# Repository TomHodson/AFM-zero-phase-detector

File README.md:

# AFM-zero-phase-detector
schematics and notes for a quartz resonator based atomic force microscope.

#Files
- sweep.py a utility to send frequency values down the serial line for testing
- AFM_stripboard_schematic schematics for the board that's built up on stripboard
- Arduino_AD9833_serial_controller an arduino sketch to control the frequency generator via the serial line.

#System components

##Frequency generator 

AD9833 arduino code
http://www.vwlowen.co.uk/arduino/AD9833-waveform-generator/AD9833-waveform-generator.htm

ad9833 datasheet
http://www.analog.com/media/en/technical-documentation/data-sheets/AD9833.pdf

AD9833 module with a 25MHz reference clock. It works by setting an ADC from a sine wave lookup table once per clock cycle. Gives reasonably clean waveforms up to about 1MHz.

controlled through SPI interface, pins are CLK and DATA along with a chip select pin called FSYNC that needs to be brought low when sending data and high to tell the chip you’re finished.

SPI mode 2 (data on falling edge of clock), MSB first

the frequency register is 28 bits long, if you set it to x then the generated frequency will be 

output frequency = x * reference frequency / (2^28)

If you read the data sheet you’ll see that you need to send the value 0x2000 to put the IC in sine wave mode. If you read the included Arduino code you’ll see it’s actually sends 0x2003 which has the last two bits set, one that should put it in triangle wave mode and one bit that’s reserved and should always be 0. I cannot explain this but it seems to generate a sine wave, 0x2000 does not.

The sine and triangle wave outputs are around 0.6v pk-pk coming from the module.

The module is currently wired up to an arduino nano. There's variable gain opamp stage that you can control from a potentiometer and another pot wired up to A7 that you can use as input to arduino sketches.

##Phase detector

Measures the phase difference between the signal coming from the frequency generator and the current through the tuning fork AFM. Does zero crossing detection on both signals, using one to start a linear ramp (555) then uses the other to trigger a sample and hold IC, outputs this value. 

sample and hold LF198 data sheet
http://www.ti.com/lit/ds/symlink/lf398-n.pdf

Note: The output of the Sample and hold IC is steady when in hold mode but shows a transient when the IC is sampling, two can be chained to negate this issue. 

Freq Generator —> tuning fork —> preamp —> zero crossing detector —> | Ramp 

Freq Generator —> zero crossing detector —————————————-> |

Signal Ranger (Interface, DACs and ADCs)

+- 10v DAC outputs to drive piezos, ADC inputs to measure phase and amplitude information.

Need some mechanism to control the 

Manufacturer page and manual
http://www.softdb.com/dsp-products-SR-MK2.php
http://www.softdb.com/_files/_dsp_division/SignalRanger_mk2_UsersManual.pdf

Needs firmware.

Driven by GXSM.

##Power supply
https://octopart.com/tmp+15515c-tracopower-8602141

Tracopower TMP 15515C
5V @ 380mA
+- 15V @ +- 150mA

May need to be loaded at 10-20% rated current to get best stability.

V1 negative appears to the 5v ground
V1 positive is 5v
V2 is 15v
V3 is -15v
Com 2/3 is GND for the +-15V rails

The two grounds appear connected and both are connected with a wire in the box to mains earth return.

##Useful links

Initial 0PM-AFM paper
https://drive.google.com/file/d/0B9IbJ1fnFICZQWVrSVRpWlJHZWFQMFR3cmFBQ0w3NExQVEFZ/view

12: describes tuning fork based AFM
http://dx.doi.org/10.1063/1.113340

9: explanation of dissipation’s effect on resonant frequency and phase
http://dx.doi.org/10.1063/1.2355437

15: description of phase detector:
http://dx.doi.org/10.1063/1.1149968

AD9833 arduino code
http://www.vwlowen.co.uk/arduino/AD9833-waveform-generator/AD9833-waveform-generator.htm

ad9833 datasheet
http://www.analog.com/media/en/technical-documentation/data-sheets/AD9833.pdf

sample and hold lf198 data sheet
http://www.ti.com/lit/ds/symlink/lf398-n.pdf

signal ranger page
http://www.softdb.com/dsp-products-SR-MK2.php
http://www.softdb.com/_files/_dsp_division/SignalRanger_mk2_UsersManual.pdf

A paper on the properties of quartz tuning forks
http://laplace.ucv.cl/Cursos/FisicaExperimental_2/Old/AJP000415.pdf

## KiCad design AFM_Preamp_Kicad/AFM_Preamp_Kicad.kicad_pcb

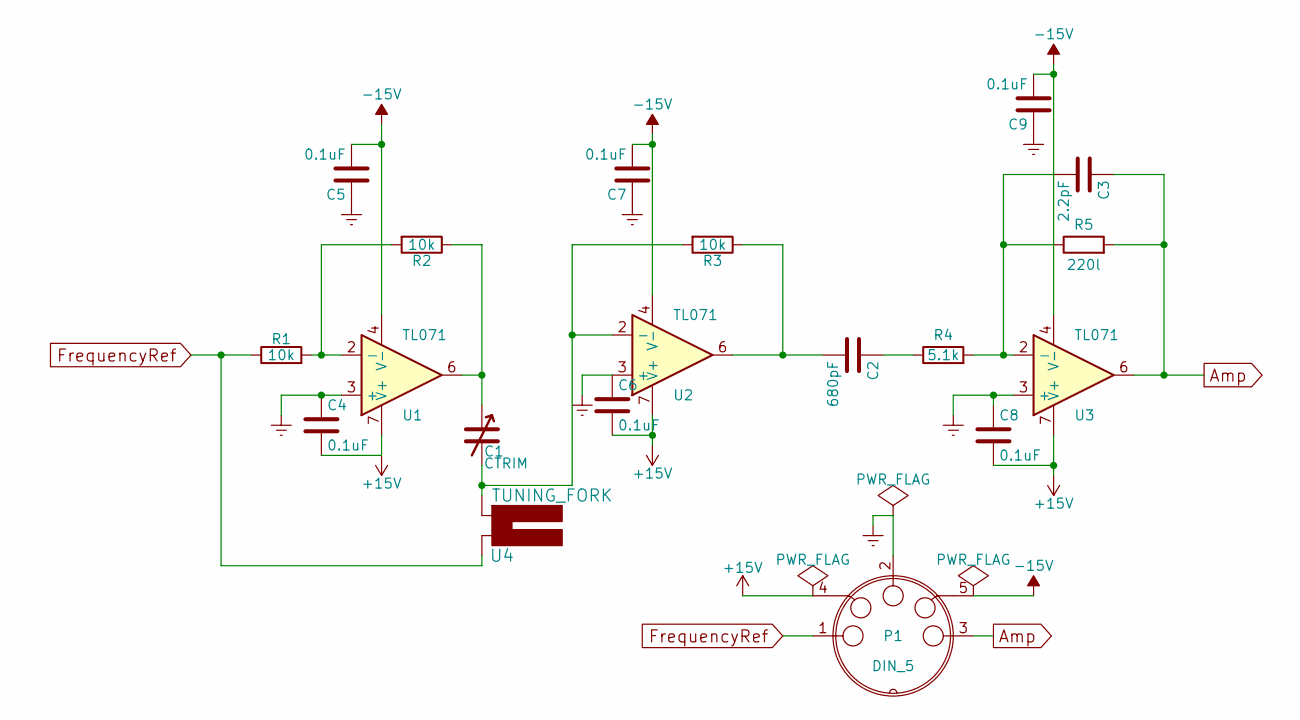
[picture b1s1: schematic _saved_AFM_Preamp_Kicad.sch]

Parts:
C1: CTRIM; C_Radial_D10_L13_P5
C2: 680pF; C_Disc_D3_P2.5
C3: 2.2pF; C_Disc_D3_P2.5
C4, C5, C6, C7, C8, C9: 0.1uF; C_Disc_D3_P2.5
P1: DIN_5; Pin_Header_Straight_1x05
R1, R2, R3: 10k; Resistor_Horizontal_RM10mm
R4: 5.1k; Resistor_Horizontal_RM10mm
R5: 220l; Resistor_Horizontal_RM10mm
U1, U2, U3: TL071; DIP-8_W7.62mm
U4: TUNING_FORK; Pin_Header_Straight_1x02

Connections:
+15V: C4.2, C6.2, C8.2, P1.4, U1.7 (V+), U2.7 (V+), U3.7 (V+)
-15V: C5.2, C7.2, C9.2, P1.5, U1.4 (V-), U2.4 (V-), U3.4 (V-)
Amp: C3.1, P1.3, R5.2, U3.6
Earth: C4.1, C5.1, C6.1, C7.1, C8.1, C9.1, P1.2, U1.3 (+), U2.3 (+), U3.3 (+)
FrequencyRef: P1.1, R1.1, U4.1
unnamed: C1.1, R2.1, U1.6
unnamed: C1.2, R3.2, U2.2 (-), U4.2
unnamed: C2.1, R4.1
unnamed: C2.2, R3.1, U2.6
unnamed: C3.2, R4.2, R5.1, U3.2 (-)
unnamed: R1.2, R2.2, U1.2 (-)

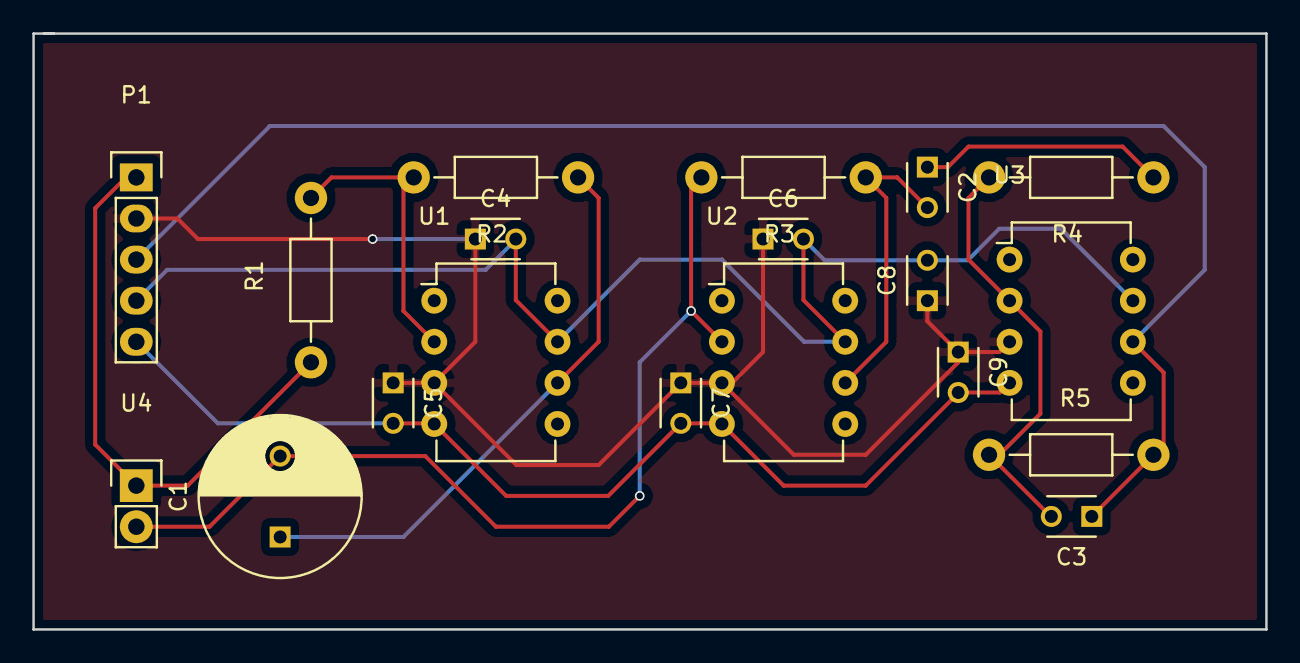
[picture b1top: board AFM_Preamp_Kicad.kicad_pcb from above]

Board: 2 copper layers, 76.2 x 36.8 mm, 19 parts (0 on the bottom side), 11 nets.

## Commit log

2016-09-18 add pic
2016-09-18 add schematics for the preamp board
2016-09-26 add preamp schematic
2016-09-26 add example arduino sketch
2016-09-26 add python examples
2016-09-26 add git ignore file
2016-09-26 add schematics for the stripboarded circuit
2016-09-27 get rid of accidental addition
2016-09-27 add frequency sweep sketch
2017-07-25 random changes
